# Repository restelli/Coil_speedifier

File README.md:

# Coil Speedifyer
This circuit can be used to interrupt current into a coil and, by allowing the emf to peak to a tunable value, speed up the turn off.
The main limitations are:
1) Reduced duty cycle: that can be changed by using a different driver circuit for the MOSFET. It turns out it was not necessary for our application
2) Speed limited by the voltage rating of the MOS. This can be changed by selecting different MOSFET (Including SiC)

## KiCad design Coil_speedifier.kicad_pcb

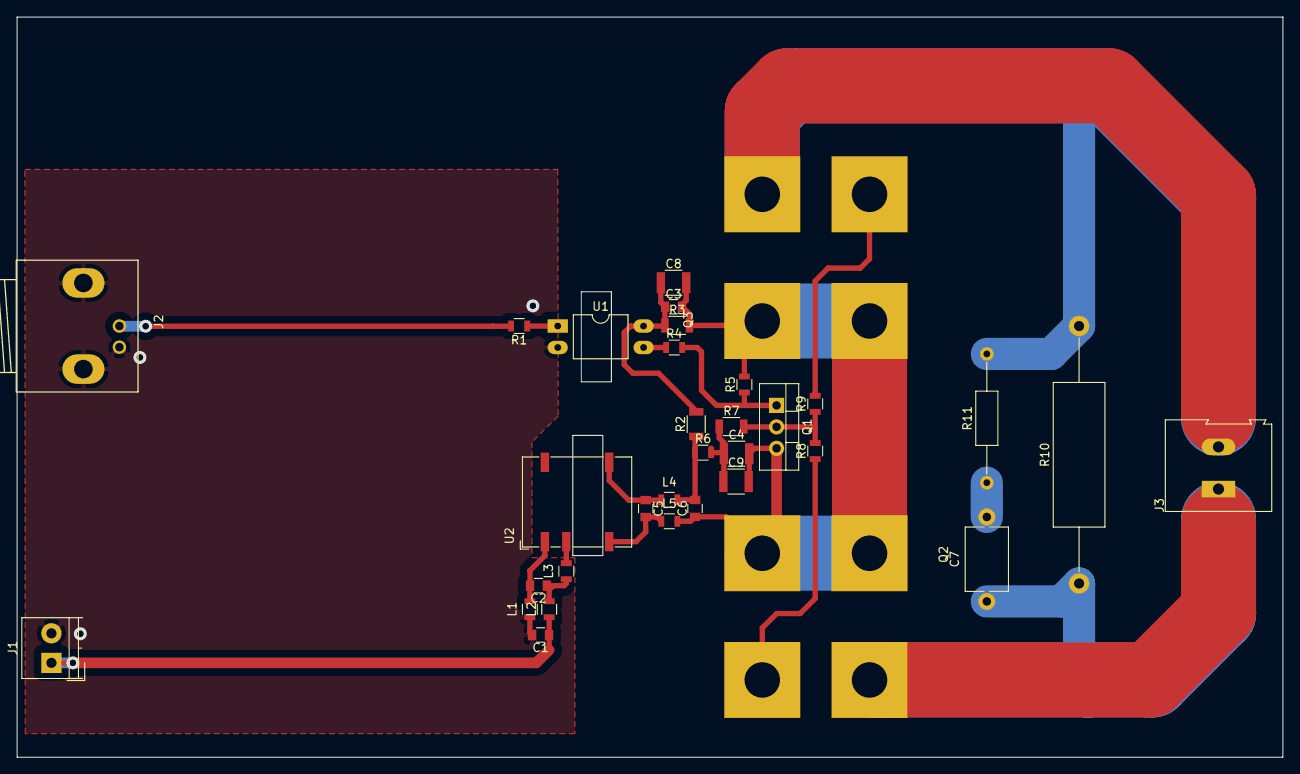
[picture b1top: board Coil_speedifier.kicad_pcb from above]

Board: 2 copper layers, 149.9 x 87.6 mm, 33 parts (0 on the bottom side), 21 nets.

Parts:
C1, C2, C3, C5, C6: C; C_0805
C4, C8, C9: C; C_1210
C7: C; C_Disc_D7.5mm_W5.0mm_P10.00mm
J1: Screw_Terminal_01x02; TerminalBlock_4UCON_19963_02x3.5mm_Straight
J2: Conn_Coaxial; BNC_Socket_TYCO-AMP
J3: Screw_Terminal_01x02; TerminalBlock_Altech_AK300-2_P5.00mm
L1, L2, L3, L4, L5: INDUCTOR; L_0805
Q1: Q_NPN_Darlington_BCE; TO-220-3_Vertical
Q2, Q3: Q_NMOS_GDS; STE250NS10
R1, R4, R5, R6, R8, R9: R_US; R_0805
R2, R3, R7: R_US; R_1206
R10: R_US; R_Axial_DIN0617_L17.0mm_D6.0mm_P30.48mm_Horizontal
R11: R_US; R_Axial_DIN0207_L6.3mm_D2.5mm_P15.24mm_Horizontal
U1: LTV-817; DIP-4_W10.16mm_LongPads
U2: PDS1-S15-S15-M; DCDC-Conv_muRata_NXE2SxxxxMC

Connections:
+15V: C6.2, L4.2, R2.1, R6.1
GND: C1.2, J1.2, J2.2, L1.1, U1.2
GNDD: C3.2, C4.2, C6.1, C8.2, C9.2, L5.2, Q1.3, Q2.3, Q3.3, R3.2, R5.2
unnamed: C1.1, J1.1, L2.1
unnamed: C2.1, L2.2, L3.1
unnamed: C2.2, L1.2, U2.1
unnamed: C3.1, C8.1, R2.2, R3.1, U1.4
unnamed: C4.1, C9.1, R6.2, R7.1
unnamed: C5.1, L4.1, U2.8
unnamed: C5.2, L5.1, U2.7
unnamed: C7.1, J3.1, Q2.2, R10.1
unnamed: C7.2, R11.1
unnamed: J2.1, R1.2
unnamed: J3.2, Q3.2, R10.2, R11.2
unnamed: L3.2, U2.3
unnamed: Q1.1, R4.2, R5.1
unnamed: Q1.2, R7.2, R8.2, R9.1
unnamed: Q2.1, R8.1
unnamed: Q3.1, R9.2
unnamed: R1.1, U1.1
unnamed: R4.1, U1.3

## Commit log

2024-04-24 updated to version 8
2024-04-24 Adding more info on README
